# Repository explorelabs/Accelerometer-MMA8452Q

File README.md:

Accelerometer-MMA8452Q
======================

This repo contains schematic and EAGLE design files for the Freescale Semiconductor's MMA8452Q accelerometer.

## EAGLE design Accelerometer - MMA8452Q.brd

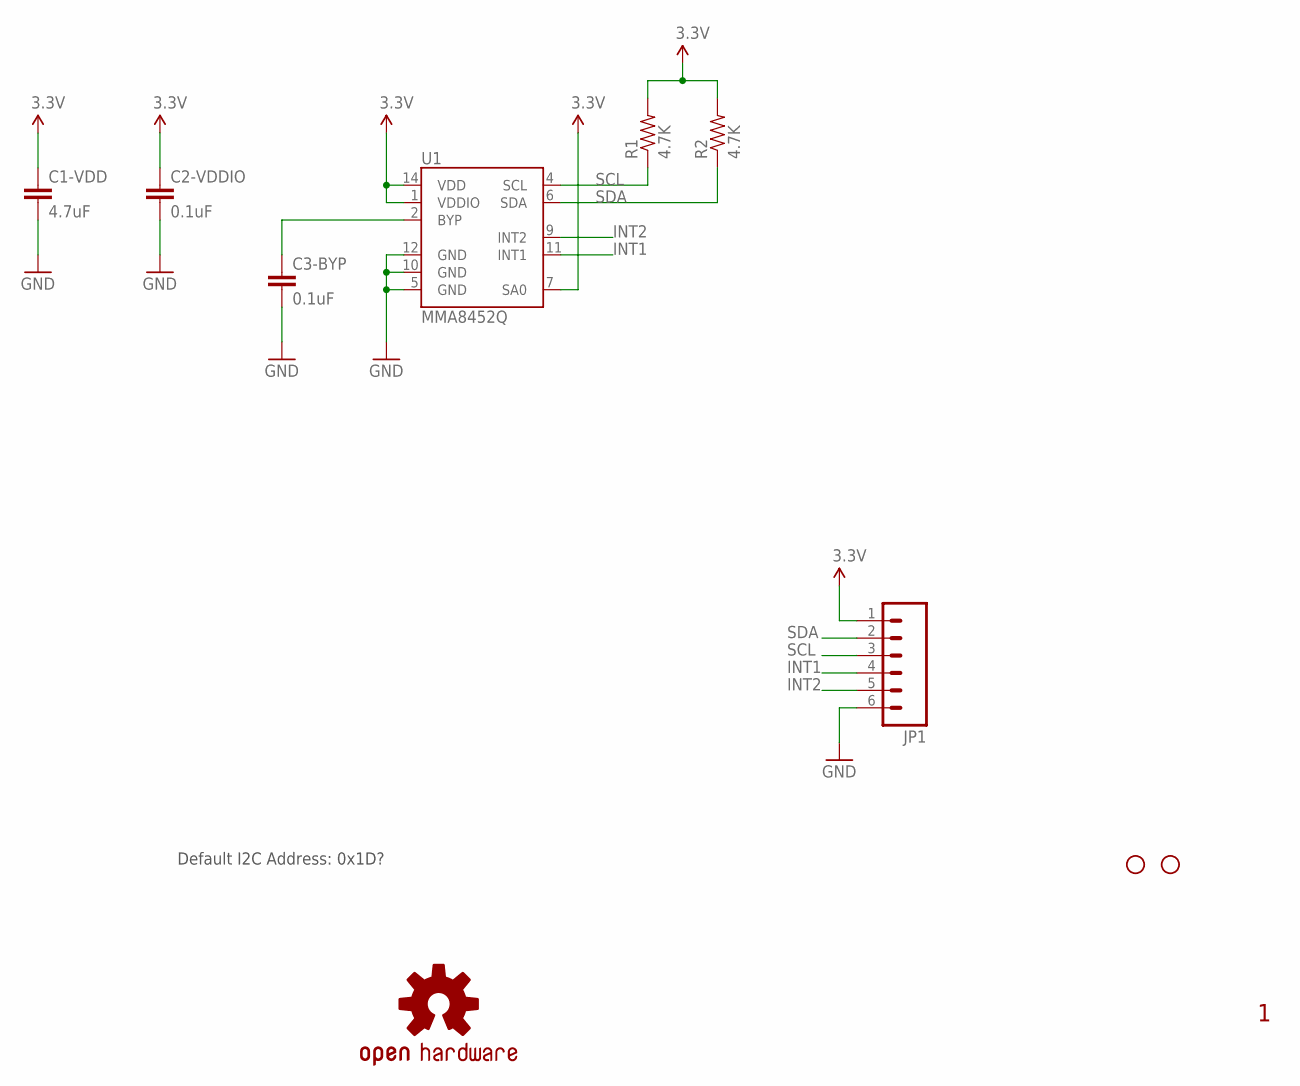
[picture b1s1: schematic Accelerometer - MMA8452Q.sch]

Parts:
C1-VDD: 4.7uF; 0603-CAP
C2-VDDIO, C3-BYP: 0.1uF; 0603-CAP
JP1: M06SILK_FEMALE_PTH; 1X06
LOGO1: OSHW-LOGOS; OSHW-LOGO-S
R1, R2: 4.7K; 0603-RES
STANDOFF1, STANDOFF2: STAND-OFFTIGHT; STAND-OFF-TIGHT
U1: MMA8452Q; QFN-16_0.5MM

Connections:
3.3V: C1-VDD.1, C2-VDDIO.1, JP1.1, R1.2, R2.2, U1.1 (VDDIO), U1.7 (SA0), U1.14 (VDD)
GND: C1-VDD.2, C2-VDDIO.2, C3-BYP.2, JP1.6, U1.5 (GND), U1.10 (GND), U1.12 (GND)
INT1: JP1.4, U1.11 (INT1)
INT2: JP1.5, U1.9 (INT2)
unnamed: C3-BYP.1, U1.2 (BYP)
SCL: JP1.3, R1.1, U1.4 (SCL)
SDA: JP1.2, R2.1, U1.6 (SDA)

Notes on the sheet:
Default I2C Address: 0x1D?

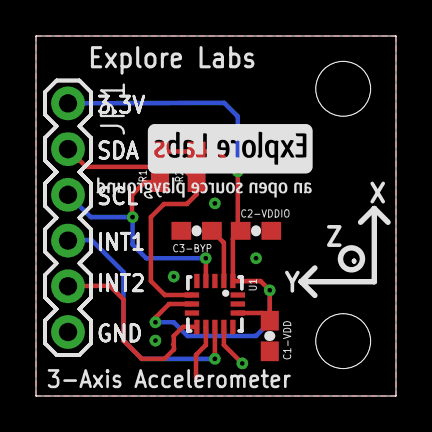
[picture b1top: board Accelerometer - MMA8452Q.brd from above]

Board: 2 copper layers, 20.0 x 20.0 mm, 12 parts (1 on the bottom side), 7 nets.

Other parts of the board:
U$1: OSHW-LOGO-M-BOTTOM
U$7: EXLABS_LOGO_0.25

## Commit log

2014-12-08 initial commit
    first commit

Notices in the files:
parts and their libraries:
SparkFun-Passives: Licensing: Creative Commons ShareAlike 4.0 International - https://creativecommons.org/licenses/by-sa/4.0
Explore Labs EAGLE Library: Released under the Creative Commons
Explore Labs EAGLE Library: http://creativecommons.org/licenses/by-sa/4.0
